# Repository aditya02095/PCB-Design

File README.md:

# PCB-Design
Here are the gerber files for the digital frequency meter created using KiCAD

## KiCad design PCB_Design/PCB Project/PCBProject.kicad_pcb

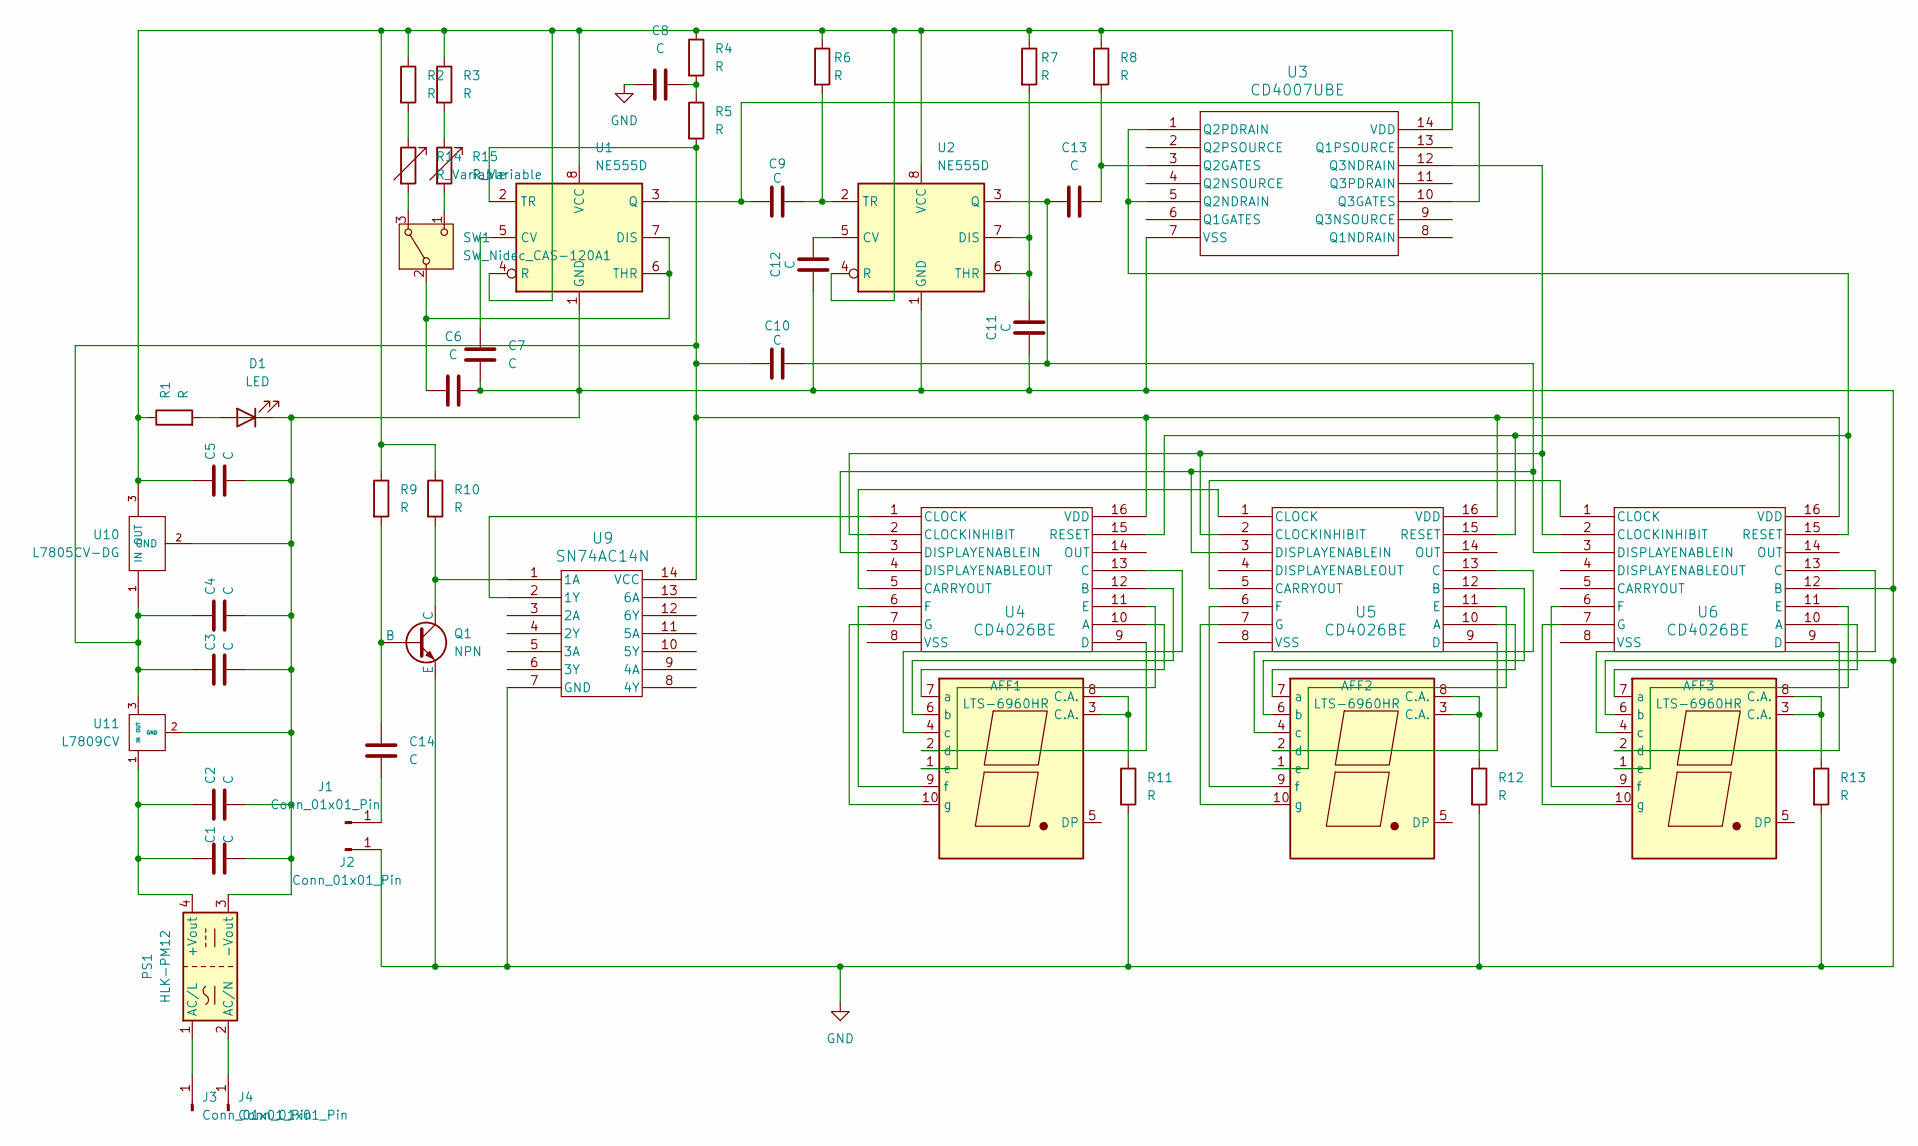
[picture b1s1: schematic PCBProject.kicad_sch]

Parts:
AFF1, AFF2, AFF3: LTS-6960HR; 7SegmentLED_LTS6760_LTS6780
C1, C2, C3, C4, C5, C6, C7, C8, C9, C10, C11, C12, C13, C14: C; CP_Elec_3x5.3
D1: LED; LED_Dialight_591
J1, J2, J3, J4: Conn_01x01_Pin; Samtec_HPM-01-01-x-S_Straight_1x01_Pitch5.08mm
PS1: HLK-PM12; Converter_ACDC_Hi-Link_HLK-PMxx
Q1: NPN; MMBT3904_7_F
R1, R2, R3, R4, R5, R6, R7, R8, R9, R10, R11, R12, R13: R; R_Axial_DIN0204_L3.6mm_D1.6mm_P5.08mm_Horizontal
R14, R15: R_Variable; R_Axial_DIN0204_L3.6mm_D1.6mm_P5.08mm_Horizontal
SW1: SW_Nidec_CAS-120A1; Nidec_Copal_CAS-120A
U1, U2: NE555D; SOIC-8_3.9x4.9mm_P1.27mm
U3: CD4007UBE; N14
U4, U5, U6: CD4026BE; N16
U9: SN74AC14N; N14
U10: L7805CV-DG; L7805CV; PARTREV 36
U11: L7809CV; PARTREV 36

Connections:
GND: AFF3.6 (b), C1.2, C2.2, C3.2, C4.2, C5.2, C6.2, C7.2, C8.1, C11.1, C12.1, D1.1 (K), J2.1, PS1.3 (-Vout), Q1.3 (E), R11.2, R12.2, R13.2, U1.1 (GND), U2.1 (GND), U3.7 (VSS), U6.12 (B), U9.7 (GND), U10.2 (GND), U11.2 (GND)
unnamed: AFF1.3 (C.A.), AFF1.8 (C.A.), R11.1
unnamed: AFF1.7 (a), U4.10 (A)
unnamed: AFF1.6 (b), U4.12 (B)
unnamed: AFF1.4 (c), U4.13 (C)
unnamed: AFF1.2 (d), U4.9 (D)
unnamed: AFF1.1 (e), U4.11 (E)
unnamed: AFF1.9 (f), U4.6 (F)
unnamed: AFF1.10 (g), U4.7 (G)
unnamed: AFF2.3 (C.A.), AFF2.8 (C.A.), R12.1
unnamed: AFF2.7 (a), U5.10 (A)
unnamed: AFF2.6 (b), U5.12 (B)
unnamed: AFF2.4 (c), U5.13 (C)
unnamed: AFF2.2 (d), U5.9 (D)
unnamed: AFF2.1 (e), U5.11 (E)
unnamed: AFF2.9 (f), U5.6 (F)
unnamed: AFF2.10 (g), U5.7 (G)
unnamed: AFF3.3 (C.A.), AFF3.8 (C.A.), R13.1
unnamed: AFF3.7 (a), U6.10 (A)
unnamed: AFF3.4 (c), U6.13 (C)
unnamed: AFF3.2 (d), U6.9 (D)
unnamed: AFF3.1 (e), U6.11 (E)
unnamed: AFF3.9 (f), U6.6 (F)
unnamed: AFF3.10 (g), U6.7 (G)
unnamed: C8.2, R4.2, R5.1
unnamed: D1.2 (A), R1.2
unnamed: C14.1, J1.1
unnamed: J3.1, PS1.1 (AC/L)
unnamed: J4.1, PS1.2 (AC/N)
unnamed: C1.1, C2.1, PS1.4 (+Vout), U11.1 (IN)
unnamed: C14.2, Q1.2 (B), R9.2
unnamed: Q1.1 (C), R10.2, U9.1 (1A)
unnamed: R2.2, R14.1
unnamed: R3.2, R15.1
unnamed: R14.2, SW1.3 (A)
unnamed: C6.1, SW1.2 (B), U1.6 (THR), U1.7 (DIS)
unnamed: R15.2, SW1.1 (C)
unnamed: C7.1, U1.5 (CV)
unnamed: C9.1, U1.3 (Q), U3.10 (Q3GATES)
unnamed: C5.1, R1.1, R2.1, R3.1, R4.1, R6.1, R7.1, R8.1, R9.1, R10.1, U1.4 (R), U1.8 (VCC), U2.4 (R), U2.8 (VCC), U3.14 (VDD), U10.3 (OUT)
unnamed: C3.1, C4.1, C10.1, R5.2, U1.2 (TR), U4.16 (VDD), U5.16 (VDD), U6.16 (VDD), U9.14 (VCC), U10.1 (IN), U11.3 (OUT)
unnamed: C12.2, U2.5 (CV)
unnamed: C11.2, R7.2, U2.6 (THR), U2.7 (DIS)
unnamed: C10.2, C13.1, U2.3 (Q), U4.3 (DISPLAYENABLEIN), U5.3 (DISPLAYENABLEIN), U6.3 (DISPLAYENABLEIN)
unnamed: C9.2, R6.2, U2.2 (TR)
unnamed: C13.2, R8.2, U3.3 (Q2GATES)
unnamed: U3.1 (Q2PDRAIN), U3.5 (Q2NDRAIN), U4.15 (RESET), U5.15 (RESET), U6.15 (RESET)
unnamed: U3.12 (Q3NDRAIN), U4.2 (CLOCKINHIBIT), U5.2 (CLOCKINHIBIT), U6.2 (CLOCKINHIBIT)
unnamed: U4.5 (CARRYOUT), U5.1 (CLOCK)
unnamed: U4.1 (CLOCK), U9.2 (1Y)
unnamed: U5.5 (CARRYOUT), U6.1 (CLOCK)

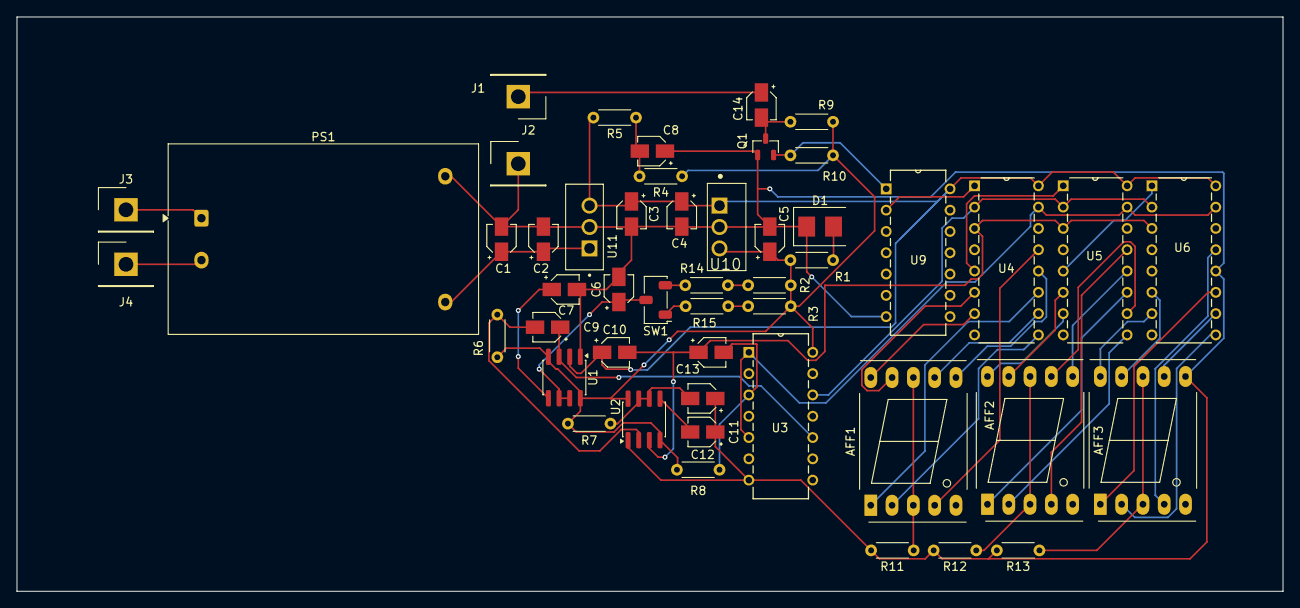
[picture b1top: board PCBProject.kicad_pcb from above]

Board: 2 copper layers, 151.0 x 68.5 mm, 49 parts (0 on the bottom side), 51 nets.
